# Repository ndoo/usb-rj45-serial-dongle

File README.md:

# USB RJ-45 Serial Dongle

A small USB to RS232 serial dongle, presented as a female RJ-45 jack that can be used with your choice of straight-through cable. Pinout is stanard Cisco RJ-45 console. Compatibility may vary with other vendors.

## Motivation

Commercial USB to Cisco-style serial cables are generally a single molded assembly, which means any issues with the RJ-45 jack (such as retention clip breaking) or forceful disconnection such as dropping your laptop, may neccesitate replacing the entire dongle.

By presenting a female RJ-45 jack, you now have the freedom to choose any length and quality of straight-through Ethernet cable, and replace it as clips break.

## Bill of Materials and Ordering

| Designator        | MPN                 | Qty | Link                                                                                                       |
|-------------------|---------------------|-----|------------------------------------------------------------------------------------------------------------|
| C1,C3             | CC0402MRX5R5BB475   | 2   |                                                                                                            |
| C2,C4,C5,C6,C7,C8 | CC0402KRX7R8BB104   | 6   |                                                                                                            |
| R1                | RC0402FR-071KL      | 1   |                                                                                                            |
| R2,R3             | RC0402FR-07330RL    | 2   |                                                                                                            |
| R4                | RC0402FR-0722KL     | 1   |                                                                                                            |
| R5                | RC0402FR-0747KL     | 1   |                                                                                                            |
| U1                | CP2102N-A01-GQFN20R | 1   | https://www.digikey.sg/product-detail/en/silicon-labs/CP2102N-A01-GQFN20R/336-4826-1-ND/8619802            |
| U2                | MAX202ECWE+         | 1   | https://www.digikey.sg/product-detail/en/maxim-integrated/MAX202ECWE/MAX202ECWE-ND/947811                  |
| U3                | SP0503BAHTG         | 1   | https://www.digikey.sg/product-detail/en/littelfuse-inc/SP0503BAHTG/F2715CT-ND/1154322                     |
| J1                | RJHSE-5081          | 1   | https://www.digikey.sg/product-detail/en/amphenol-icc-commercial-products/RJHSE-5081/RJHSE-5081-ND/1242688 |

## License

This project is licensed under the MIT License - see the [LICENSE.md](LICENSE.md) file for details

## Acknowledgments

* USB connector is from USBPCB from Sparkfun's EAGLE libraries

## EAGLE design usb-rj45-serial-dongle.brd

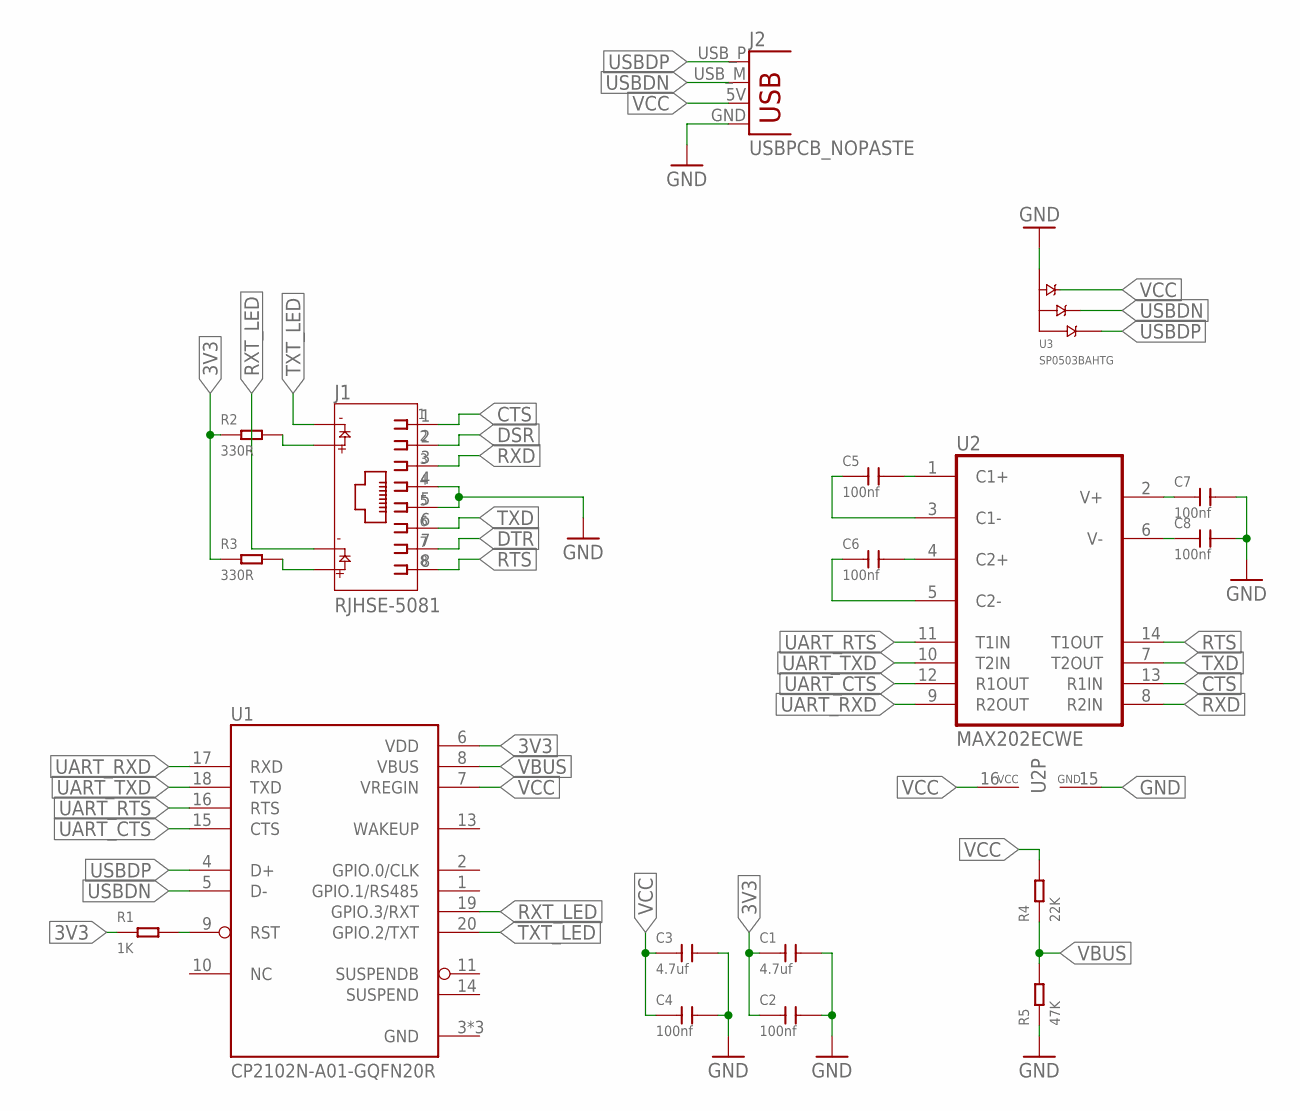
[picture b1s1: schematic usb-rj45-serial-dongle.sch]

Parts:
C1, C3: 4.7uf; C0402
C2, C4, C5, C6, C7, C8: 100nf; C0402
J1: RJHSE-5081
J2: USBPCB_NOPASTE; USB-A-PCB-NOPASTE
R1: 1K; R0402
R2, R3: 330R; R0402
R4: 22K; R0402
R5: 47K; R0402
U1: CP2102N-A01-GQFN20R; SILABS_QFN20
U2: MAX202ECWE; SO16L
U3: SP0503BAHTG; SOT143

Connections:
3V3: C1.1, C2.1, R1.1, R2.1, R3.1, U1.6 (VDD)
CTS: J1.1, U2.13 (R1IN)
DSR: J1.2
DTR: J1.7
GND: C1.2, C2.2, C3.2, C4.2, C7.2, C8.2, J1.4, J1.5, J2.GND, R5.1, U1.3 (GND), U1.12 (GND), U1.21 (GND), U2.15 (GND), U3.1 (GND)
unnamed: C5.2, U2.1 (C1+)
unnamed: R1.2, U1.9 (RST)
unnamed: J1.12, R3.2
unnamed: C6.2, U2.4 (C2+)
unnamed: J1.10, R2.2
unnamed: C5.1, U2.3 (C1-)
unnamed: C6.1, U2.5 (C2-)
unnamed: C7.1, U2.2 (V+)
unnamed: C8.1, U2.6 (V-)
RTS: J1.8, U2.14 (T1OUT)
RXD: J1.3, U2.8 (R2IN)
RXT_LED: J1.11, U1.19 (GPIO.3/RXT)
TXD: J1.6, U2.7 (T2OUT)
TXT_LED: J1.9, U1.20 (GPIO.2/TXT)
UART_CTS: U1.15 (CTS), U2.12 (R1OUT)
UART_RTS: U1.16 (RTS), U2.11 (T1IN)
UART_RXD: U1.17 (RXD), U2.9 (R2OUT)
UART_TXD: U1.18 (TXD), U2.10 (T2IN)
USBDN: J2.USB_M (D-), U1.5 (D-), U3.3 (B)
USBDP: J2.USB_P (D+), U1.4 (D+), U3.4 (C)
VBUS: R4.1, R5.2, U1.8 (VBUS)
VCC: C3.1, C4.1, J2.5V (VBUS), R4.2, U1.7 (VREGIN), U2.16 (VCC), U3.2 (A)

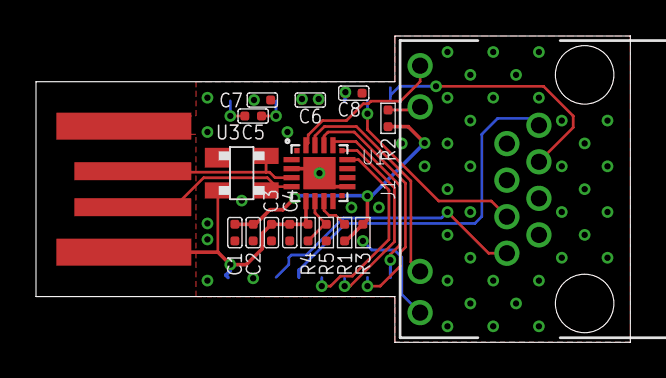
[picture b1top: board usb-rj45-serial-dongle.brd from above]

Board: 2 copper layers, 33.0 x 17.0 mm, 18 parts (1 on the bottom side), 25 nets.

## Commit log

2019-11-09 Board updates, silkscreen cleanup and component changes
    Board updates:
    - GND plane stitching changed to a more general pattern rather than closely stitched to signal lines, since we aren't doing RF
    - GND plane optimizations (bottom layer no longer separated into 2 distinct planes)
    - Reduced size of board
    Silkscreen cleanup:
    - Removed values
2019-11-09 Renumber resistors to start from R1
2019-11-09 Renumber IC1 and other ICs to be in sequence with prefix "U"
2019-11-09 Add bill of materials
2019-11-09 Use CP2102 TXT/RXT pins to drive LEDs, thanks @MatsK for pointing this feature out
2019-11-11 Add VBUS voltage divider per CP2102N datasheet; Fix CTS/RXD swapped at MAX202E; Routing improvements
2019-11-11 Review and approve ERC errors/warnings
2019-11-14 Update bill of materials with R4 and R5

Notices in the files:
parts and their libraries:
SparkFun-Connectors: Licensing: Creative Commons ShareAlike 4.0 International - https://creativecommons.org/licenses/by-sa/4.0
